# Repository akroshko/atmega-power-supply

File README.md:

A Variable-Voltage Constant-Current ATMega-based Power Supply
=============================================================

This project is a challenge to myself to build the best
variable-voltage constant-current power supply I could based on
ubiquitous components such as the LM317 voltage regulator, LM358 or
ATMega328 microcontroller.

The design is loosely based off of
[https://www.youtube.com/playlist?list=PLBF35875F73B5C9B5](https://www.youtube.com/playlist?list=PLBF35875F73B5C9B5)
by EEVblog.  However, it uses components I cannot obtain such as the
LT3080.

# Things to do

I wouldn't recommend building it yourself quite yet.  There are some
issues with this design and there will be a version 1.1
at some point.

- add a photo of my prototype
- test prototype under different loads
- add a model to calibrate to in software
- use an easier-to-get LCD display
- add a bill of materials

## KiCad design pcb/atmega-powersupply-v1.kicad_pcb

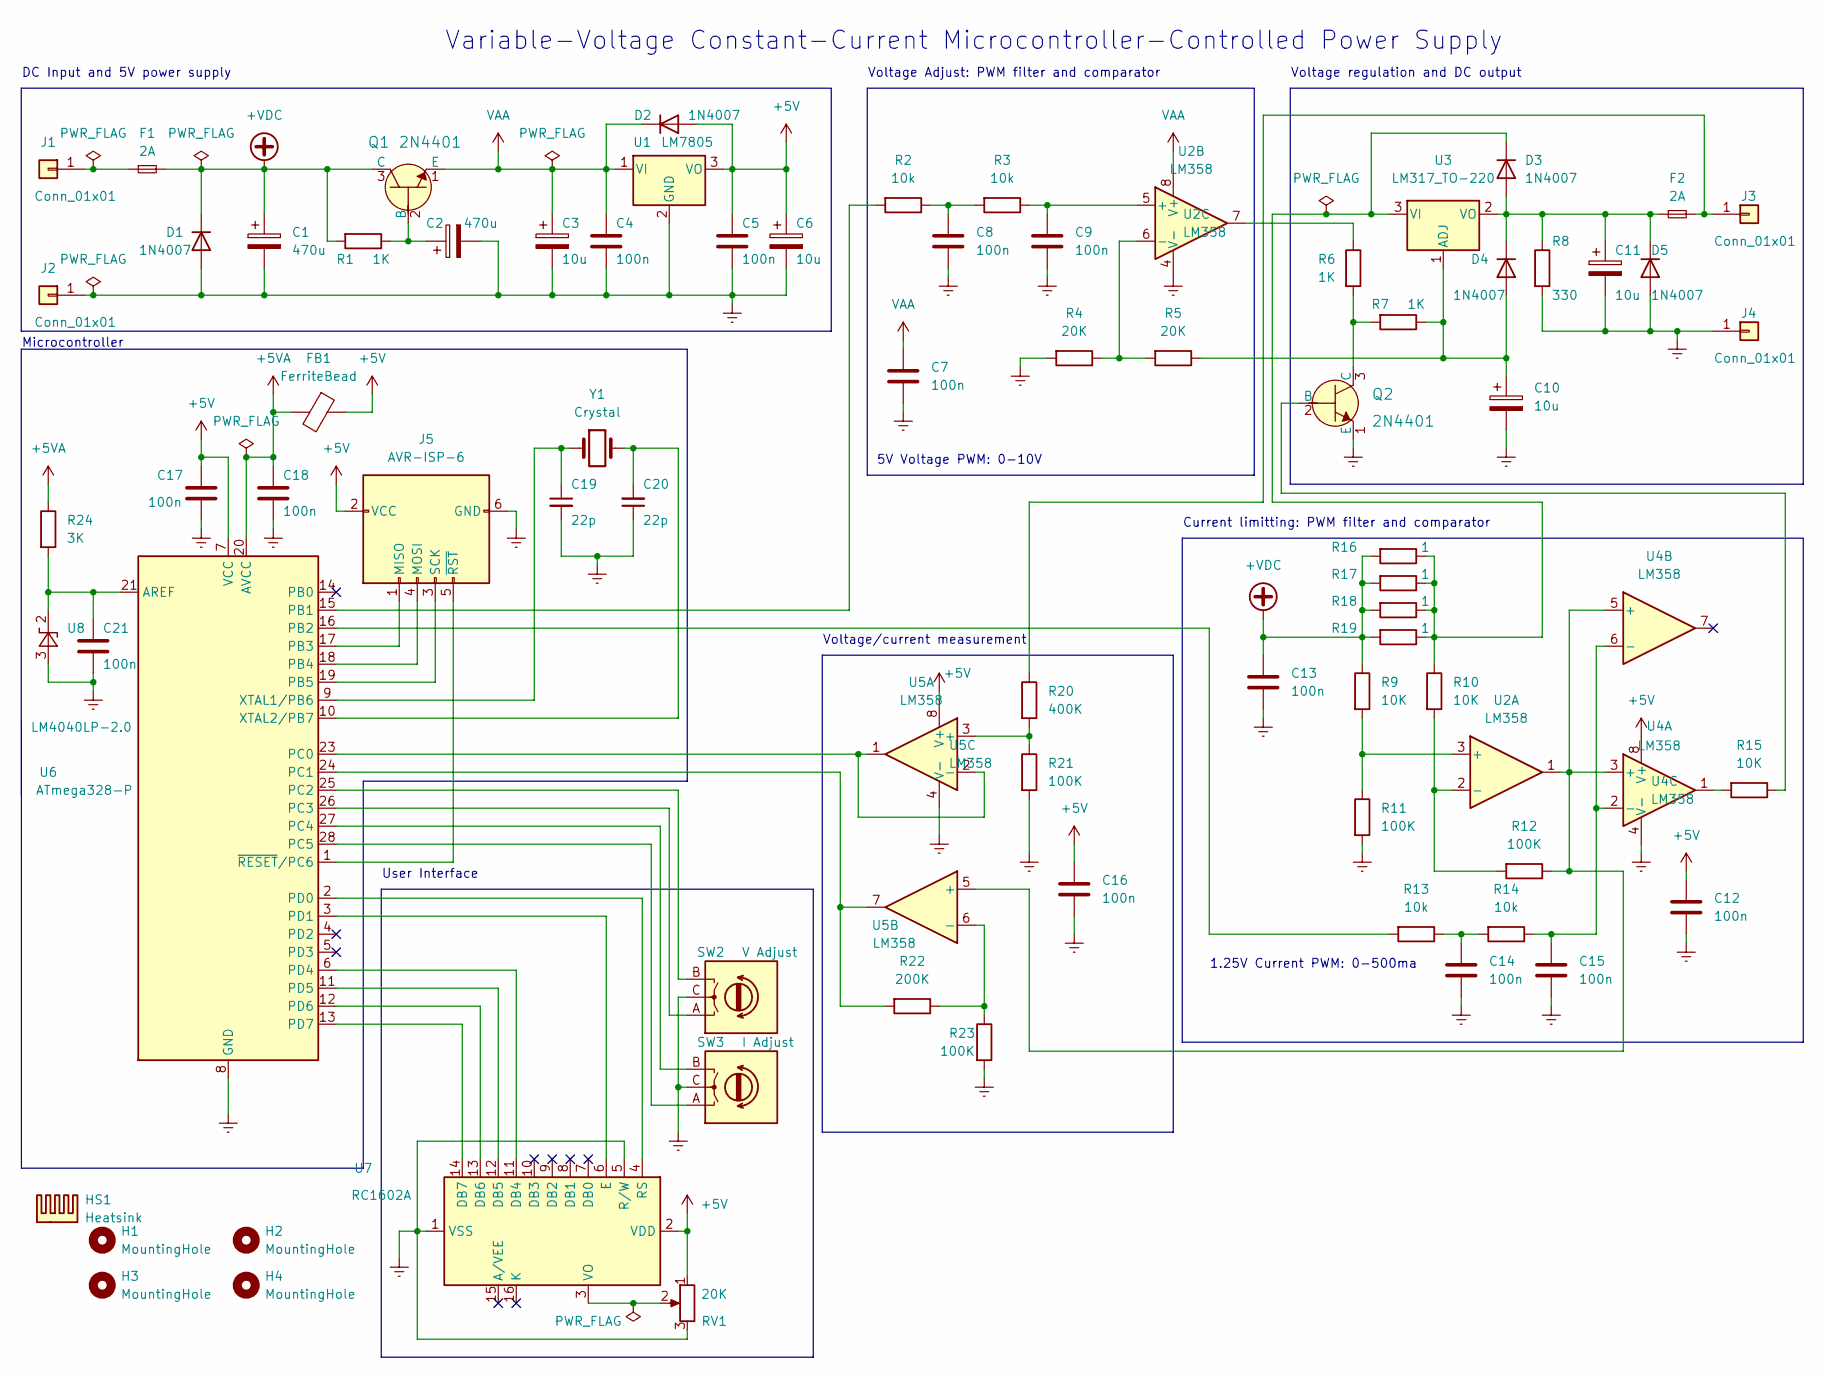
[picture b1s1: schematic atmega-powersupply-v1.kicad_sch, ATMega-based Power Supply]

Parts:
C1, C2: 470u; CP_Radial_D10.0mm_P5.00mm
C3, C6, C10, C11: 10u; CP_Radial_D5.0mm_P2.00mm
C4, C5, C7, C8, C9, C12, C13, C14, C15, C16, C17, C18, C21: 100n; C_Rect_L7.0mm_W2.5mm_P5.00mm
C19, C20: 22p; C_Rect_L7.0mm_W2.5mm_P5.00mm
D1, D2, D3, D4, D5: 1N4007; D_DO-41_SOD81_P10.16mm_Horizontal
F1, F2: 2A; Fuseholder_Littelfuse_100_series_5x20mm
FB1: FerriteBead; R_Axial_DIN0411_L9.9mm_D3.6mm_P12.70mm_Horizontal
H1, H2, H3, H4: MountingHole; MountingHole_4.3mm_M4
HS1: Heatsink; Heatsink_Fischer_SK104-STC-STIC_35x13mm_2xDrill2.5mm
J1, J2, J3, J4: Conn_01x01; Banana_Jack_1Pin
J5: AVR-ISP-6; PinHeader_2x03_P2.54mm_Vertical
Q1, Q2: 2N4401; TO-92L_Inline; MPN 2N4401TFR; Digi-Key_PN 2N4401D26ZCT-ND
R1, R6, R7: 1K; R_Axial_DIN0207_L6.3mm_D2.5mm_P7.62mm_Horizontal
R2, R3, R13, R14: 10k; R_Axial_DIN0207_L6.3mm_D2.5mm_P7.62mm_Horizontal
R4, R5: 20K; R_Axial_DIN0207_L6.3mm_D2.5mm_P7.62mm_Horizontal
R8: 330; R_Axial_DIN0207_L6.3mm_D2.5mm_P7.62mm_Horizontal
R9, R10, R15: 10K; R_Axial_DIN0207_L6.3mm_D2.5mm_P7.62mm_Horizontal
R11, R12, R21, R23: 100K; R_Axial_DIN0207_L6.3mm_D2.5mm_P7.62mm_Horizontal
R16, R17, R18, R19: 1; R_Axial_DIN0207_L6.3mm_D2.5mm_P7.62mm_Horizontal
R20: 400K; R_Axial_DIN0207_L6.3mm_D2.5mm_P7.62mm_Horizontal
R22: 200K; R_Axial_DIN0207_L6.3mm_D2.5mm_P7.62mm_Horizontal
R24: 3K; R_Axial_DIN0207_L6.3mm_D2.5mm_P7.62mm_Horizontal
RV1: 20K; Potentiometer_Alps_RK09L_Single_Vertical
SW2: V Adjust; RotaryEncoder_Alps_EC11E_Vertical_H20mm
SW3: I Adjust; RotaryEncoder_Alps_EC11E_Vertical_H20mm
U1: LM7805; TO-220-3_Vertical
U2, U4, U5: LM358; DIP-8_W7.62mm_Socket
U3: LM317_TO-220; TO-220-3_Vertical
U6: ATmega328-P; DIP-28_W7.62mm_Socket
U7: RC1602A
U8: LM4040LP-2.0; TO-92_Inline
Y1: Crystal; Crystal_HC50_Vertical

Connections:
+5V: C5.1, C6.1, C12.1, C16.1, C17.1, D2.2 (A), FB1.1, J5.2 (VCC), RV1.1, U1.3 (VO), U4.8 (V+), U5.8 (V+), U6.7 (VCC), U7.2 (VDD)
+5VA: C18.1, FB1.2, R24.1, U6.20 (AVCC)
+VDC: C1.1, C13.1, D1.1 (K), F1.2, Q1.3 (C), R1.2, R9.1, R16.2, R17.2, R18.2, R19.2
Earth: C1.2, C2.2, C3.2, C4.2, C5.2, C6.2, C7.2, C8.2, C9.2, C10.2, C11.2, C12.2, C13.2, C14.2, C15.2, C16.2, C17.2, C18.2, C19.2, C20.1, C21.2, D1.2 (A), D5.2 (A), J2.1, J4.1, J5.6 (GND), Q2.1 (E), R4.2, R8.2, R11.2, R21.2, R23.2, RV1.3, SW2.C, SW3.C, U1.2 (GND), U2.4 (V-), U4.4 (V-), U5.4 (V-), U6.8 (GND), U6.22 (GND), U7.1 (VSS), U7.5 (R/W), U8.3 (A)
unnamed: C2.1, Q1.2 (B), R1.1
unnamed: C8.1, R2.1, R3.2
unnamed: C9.1, R3.1, U2.5 (+)
unnamed: C10.1, D4.2 (A), R5.1, R7.1, U3.1 (ADJ)
unnamed: C11.1, D3.2 (A), D4.1 (K), D5.1 (K), F2.1, R8.1, U3.2 (VO)
unnamed: C14.1, R13.1, R14.2
unnamed: C15.1, R14.1, U4.2 (-), U4.6 (-)
unnamed: C19.1, U6.9 (XTAL1/PB6), Y1.1
unnamed: C20.2, U6.10 (XTAL2/PB7), Y1.2
unnamed: C21.1, R24.2, U6.21 (AREF), U8.2 (K)
unnamed: D3.1 (K), R10.1, R16.1, R17.1, R18.1, R19.1, U3.3 (VI)
unnamed: F1.1, J1.1
unnamed: F2.2, J3.1, R20.1
unnamed: J5.1 (MISO), U6.17 (PB3)
unnamed: J5.3 (SCK), U6.19 (PB5)
unnamed: J5.4 (MOSI), U6.18 (PB4)
unnamed: J5.5 (~RST), U6.1 (~RESET/PC6)
unnamed: Q2.2 (B), R15.1
unnamed: Q2.3 (C), R6.2, R7.2
unnamed: R2.2, U6.15 (PB1)
unnamed: R4.1, R5.2, U2.6 (-)
unnamed: R6.1, U2.7
unnamed: R10.2, R12.2, U2.2 (-)
unnamed: R9.2, R11.1, U2.3 (+)
unnamed: R12.1, U2.1, U4.3 (+), U4.5 (+), U5.5 (+)
unnamed: R13.2, U6.16 (PB2)
unnamed: R15.2, U4.1
unnamed: R20.2, R21.1, U5.3 (+)
unnamed: R22.1, R23.1, U5.6 (-)
unnamed: R22.2, U5.7, U6.24 (PC1)
unnamed: RV1.2, U7.3 (VO)
unnamed: SW2.A, U6.26 (PC3)
unnamed: SW2.B, U6.25 (PC2)
unnamed: SW3.A, U6.28 (PC5)
unnamed: SW3.B, U6.27 (PC4)
unnamed: U5.1, U5.2 (-), U6.23 (PC0)
unnamed: U6.2 (PD0), U7.4 (RS)
unnamed: U6.3 (PD1), U7.6 (E)
unnamed: U6.6 (PD4), U7.11 (DB4)
unnamed: U6.11 (PD5), U7.12 (DB5)
unnamed: U6.12 (PD6), U7.13 (DB6)
unnamed: U6.13 (PD7), U7.14 (DB7)
VAA: C3.1, C4.1, C7.1, D2.1 (K), Q1.1 (E), U1.1 (VI), U2.8 (V+)

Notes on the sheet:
Variable-Voltage Constant-Current Microcontroller-Controlled Power Supply
5V Voltage PWM: 0-10V
User Interface
Microcontroller
Voltage Adjust: PWM filter and comparator
1.25V Current PWM: 0-500ma
DC Input and 5V power supply
Current limitting: PWM filter and comparator
Voltage/current measurement
Voltage regulation and DC output

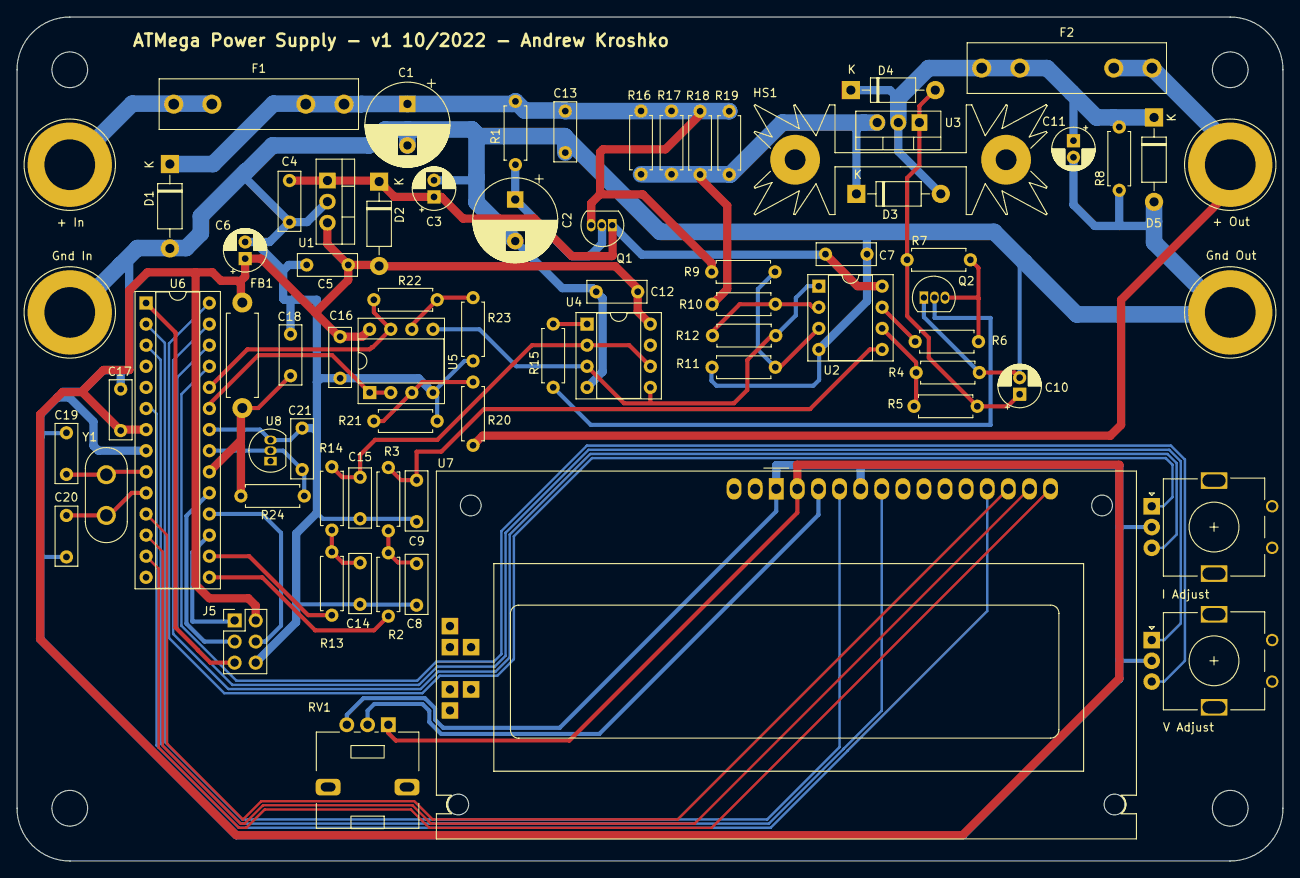
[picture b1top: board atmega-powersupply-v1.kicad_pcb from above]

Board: 2 copper layers, 152.4 x 101.6 mm, 77 parts (0 on the bottom side), 47 nets.

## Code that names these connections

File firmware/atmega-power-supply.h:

// includes configurables

////////////////////////////////////////////////////////////////////////////////
// Software values to adjust behaviour
//
// These might need to be adjusted based on swapping out different
// components
////////////////////////////////////////////////////////////////////////////////

// account for different brands of rotary encoders
#define V_DIRECTION 1
#define I_DIRECTION 0

// values for PWM
const int i_full_scale=256;
const int v_full_scale=1023;

#define INITIAL_I 0
#define INITIAL_V 0

// values for the monitor
const float VREF_VALUE=2.048;

const float V_SCALE=0.2;

const float I_SCALE_MONITOR=3.0;
const float I_SCALE_DIFF=10.0;
const float I_SENSE_R=0.25;

const uint16_t MONITOR_RAW_MAX=1024;

////////////////////////////////////////////////////////////////////////////////
// Arbitrary constants that can be used to tweak performance
////////////////////////////////////////////////////////////////////////////////

#define LCD_DELAY_US           1
#define LCD_DELAY_SEND_US    100
#define ADC_POST_DELAY_US     16

 // do analog to digital every 50 loops
#define AD_LOOP_SKIP          50

////////////////////////////////////////////////////////////////////////////////
// Constants that will generally only change with the changing the circuit itself
// _S indicates shift need for to access appropriate bit
// P_ designates the "pin", which actually maps to the individual pin of a partuclar port
//
// _ROT indicates rotary encoding
// _V indicates the rotary encoder that controls voltage
// _I indicates the rotary encoder that controls current
// _CLK indicates the rotary encoder clock pin
// _DT indicates the rotary encoder ??? pin
//
// LCD_ indicates the LCD

// _RS _E _DB4 _DB5 _DB6 _DB7 are all constants that are specific to
// pins on the LCD
////////////////////////////////////////////////////////////////////////////////

// PWM pins
const uint8_t P_PWM_V=(_BV(1)); // PB1
const uint8_t P_PWM_I=(_BV(2)); // PB2

// rotary encoder pins
#define P_ROT_V_CLK_S 2                         // PC2 SHIFT
const uint8_t P_ROT_V_CLK=(_BV(P_ROT_V_CLK_S)); // PC2
#define P_ROT_V_DT_S 3                          // PC3 SHIFT
const uint8_t P_ROT_V_DT=(_BV(P_ROT_V_DT_S));   // PC3
#define P_ROT_I_CLK_S 4                         // PC4 SHIFT
const uint8_t P_ROT_I_CLK=(_BV(P_ROT_I_CLK_S)); // PC4
#define P_ROT_I_DT_S 5                          // PC5 SHIFT
const uint8_t P_ROT_I_DT=(_BV(P_ROT_I_DT_S));   // PC5

// LCD pins
#define LCD_RS_S 0                      // PD0 SHIFT
const uint8_t LCD_RS=(_BV(LCD_RS_S));   // PD0
#define LCD_E_S  1                      // PD1 SHIFT
const uint8_t LCD_E=(_BV(LCD_E_S));     // PD1
#define LCD_DB4_S 4                     // PD4 SHIFT
const uint8_t LCD_DB4=(_BV(LCD_DB4_S)); // PD4
#define LCD_DB5_S 5                     // PD5 SHIFT
const uint8_t LCD_DB5=(_BV(LCD_DB5_S)); // PD5
#define LCD_DB6_S 6                     // PD6 SHIFT
const uint8_t LCD_DB6=(_BV(LCD_DB6_S)); // PD6
#define LCD_DB7_S 7                     // PD7 SHIFT
const uint8_t LCD_DB7=(_BV(LCD_DB7_S)); // PD7

const uint8_t LCD_PORT_D_DIRECTION_MASK=_BV(LCD_RS_S)|_BV(LCD_E_S)| \
                                        _BV(LCD_DB4_S)|_BV(LCD_DB5_S)| \
                                        _BV(LCD_DB6_S)|_BV(LCD_DB7_S);
// LCD commands
#define LCD_COMMAND_4bit_mode  0x02
#define LCD_COMMAND_2line_mode 0x28
// TODO: fill out more LCD commands after datasheet review

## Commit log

2023-04-30 initial commit of kicad files
2023-05-08 iniitial commit of Makefile
2023-05-29 initial commit of firmware
2023-05-29 some refactoring of the LCD handling
2023-05-31 refactoring stuff left over from initial experiments
2023-06-02 updating with more information such as improved schematic and README.md
2023-09-18 merged code to use A/D convertor to monitor voltage/current, general improvements and refactoring of code
